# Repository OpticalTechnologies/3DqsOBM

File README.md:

This repository contains Matlab scripts for refractive index reconstruction, simulation of the DPLD, and KiCAD design
files for the detector read-out electronics used in the manuscript 
"Enabling 3D refractive index tomography in laser scanning microscopy with a simple tape-on detector".

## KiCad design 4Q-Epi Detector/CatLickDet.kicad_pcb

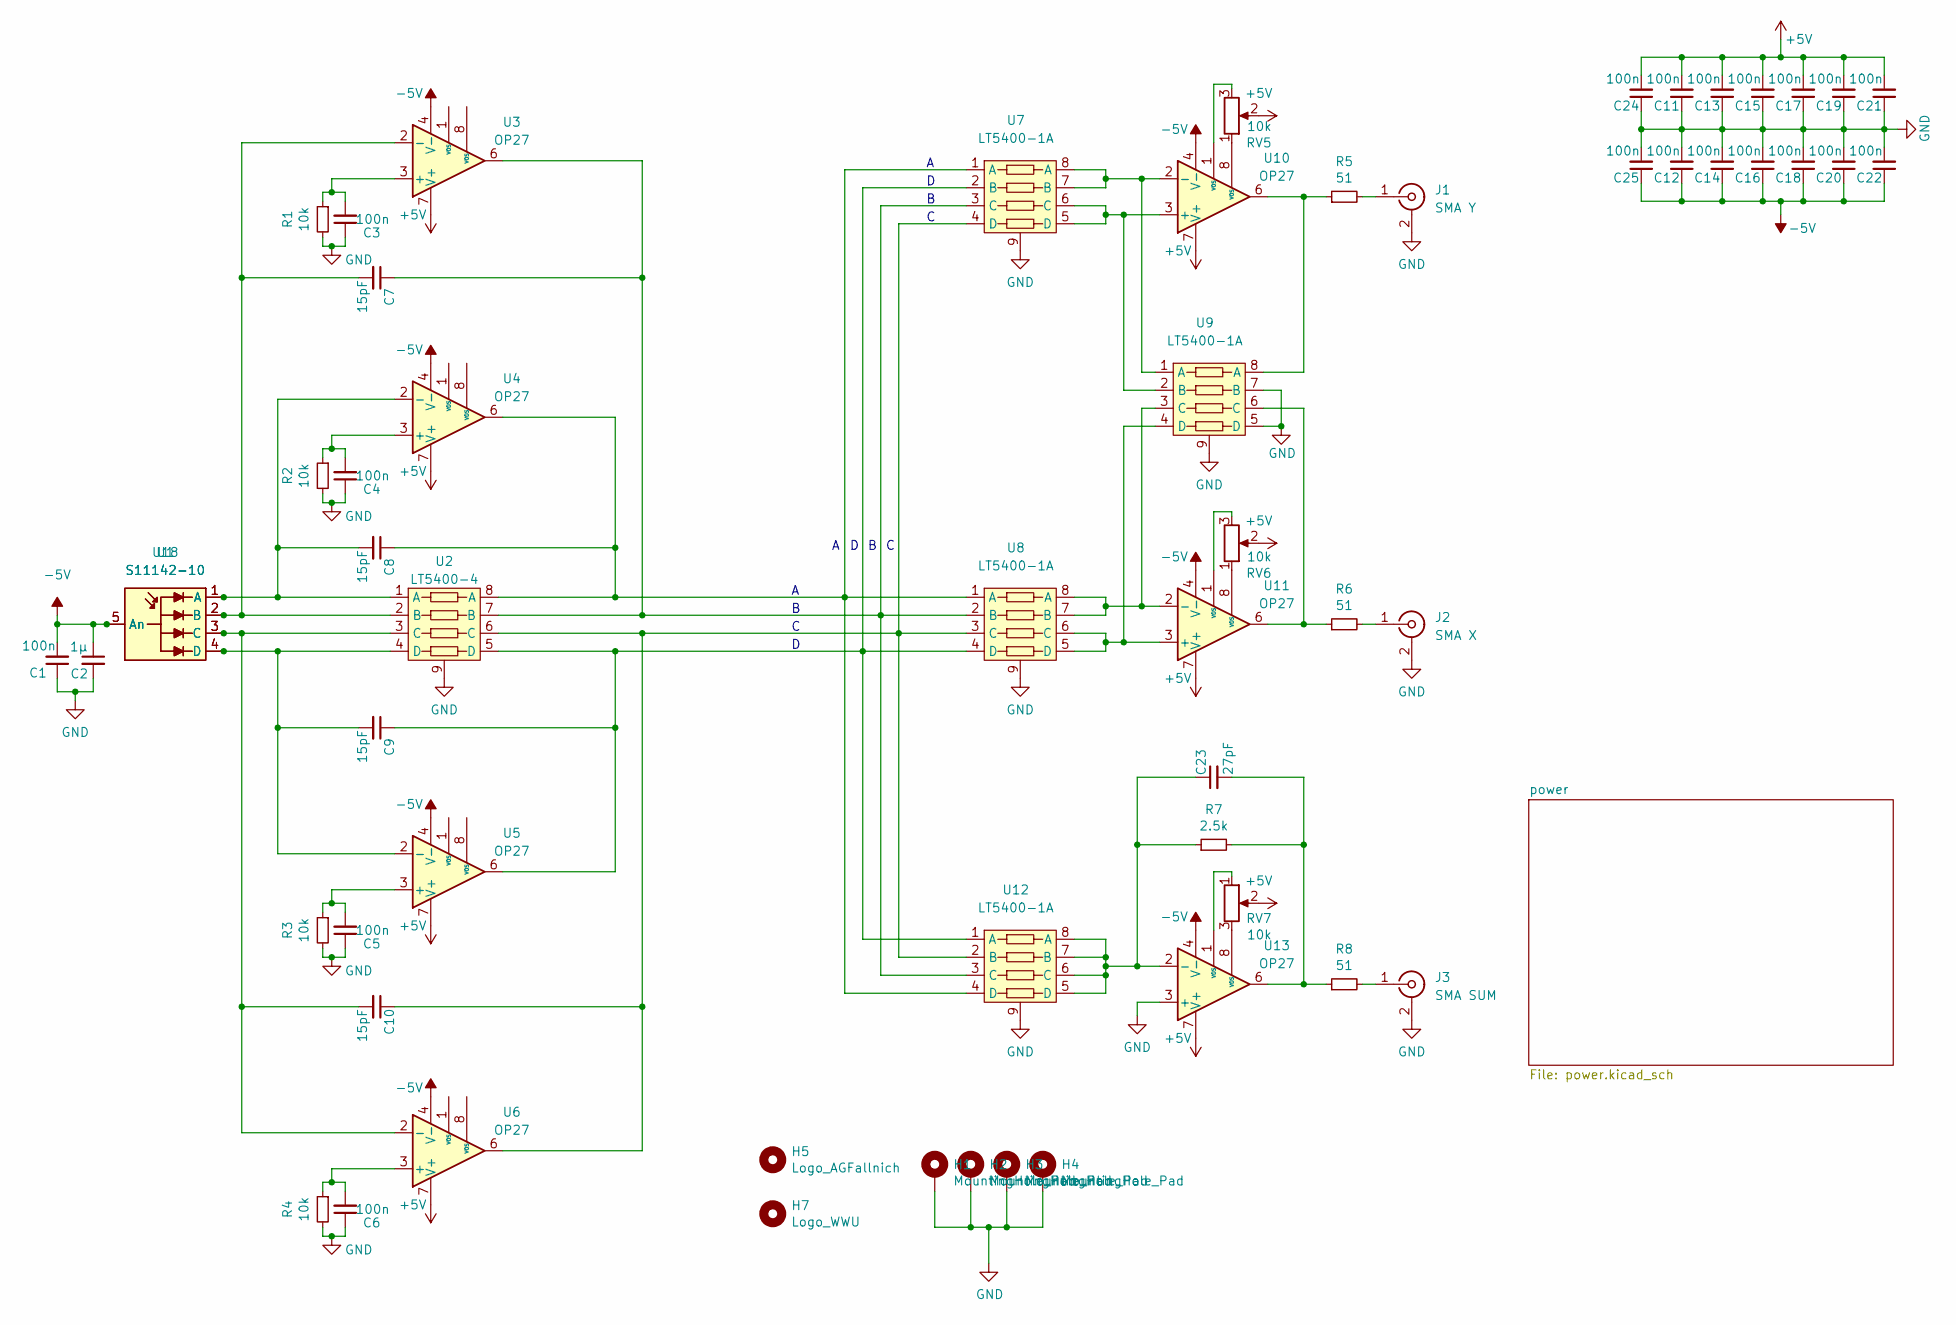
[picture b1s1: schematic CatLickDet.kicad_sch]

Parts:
C1, C3, C4, C5, C6, C11, C12, C13, C14, C15, C16, C17, C18, C19, C20, C21, C22, C24, C25: 100n; C_0402_1005Metric; LCSC C1525
C2: 1µ; C_0402_1005Metric; LCSC C52923
C7, C8, C9, C10: 15pF; C_0402_1005Metric; LCSC C1548
C23: 27pF; C_0402_1005Metric; LCSC C1557
H1, H2, H3, H4: MountingHole_Pad; MountingHole_3.2mm_M3_ISO7380_Pad
H5: Logo_AGFallnich; Logo_AGFallnich_text
H7: Logo_WWU
J1: SMA Y; SMA_Amphenol_132134-16_Vertical; Mouser 737-RF204AT0050G
J2: SMA X; SMA_Amphenol_132134-16_Vertical; Mouser 737-RF204AT0050G
J3: SMA SUM; SMA_Amphenol_132134-16_Vertical; Mouser 737-RF204AT0050G
R1, R2, R3, R4: 10k; R_0402_1005Metric; LCSC C190095
R5, R6, R8: 51; R_0402_1005Metric; LCSC C25125
R7: 2.5k; R_0603_1608Metric; LCSC C304065
RV5, RV6, RV7: 10k; Potentiometer_Bourns_3224W_Vertical; LCSC C81348
U1, U18: S11142-10
U2: LT5400-4; MSOP-8-1EP_3x3mm_P0.65mm_EP1.68x1.88mm; LCSC C1357905
U3, U4, U5, U6, U10, U11, U13: OP27; SOIC-8_3.9x4.9mm_P1.27mm; LCSC C581242
U7, U8, U9, U12: LT5400-1A; MSOP-8-1EP_3x3mm_P0.65mm_EP1.68x1.88mm; LCSC C1739156

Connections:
+5V: C11.2, C13.2, C15.2, C17.2, C19.2, C21.2, C24.2, RV5.2, RV6.2, RV7.2, U3.7 (V+), U4.7 (V+), U5.7 (V+), U6.7 (V+), U10.7 (V+), U11.7 (V+), U13.7 (V+); also elsewhere on the board
-5V: C1.2, C2.1, C12.1, C14.1, C16.1, C18.1, C20.1, C22.1, C25.1, U1.5 (An), U3.4 (V-), U4.4 (V-), U5.4 (V-), U6.4 (V-), U10.4 (V-), U11.4 (V-), U13.4 (V-), U18.5 (An); also elsewhere on the board
GND: C1.1, C2.2, C3.1, C4.1, C5.1, C6.1, C11.1, C12.2, C13.1, C14.2, C15.1, C16.2, C17.1, C18.2, C19.1, C20.2, C21.1, C22.2, C24.1, C25.2, H1.1, H2.1, H3.1, H4.1, J1.2 (Ext), J2.2 (Ext), J3.2 (Ext), R1.2, R2.2, R3.2, R4.2, U2.9, U7.9, U8.9, U9.5 (D), U9.7 (B), U9.9, U12.9, U13.3 (+); also elsewhere on the board
unnamed: C3.2, R1.1, U3.3 (+)
unnamed: C4.2, R2.1, U4.3 (+)
unnamed: C5.2, R3.1, U5.3 (+)
unnamed: C6.2, R4.1, U6.3 (+)
unnamed: C7.1, U2.7 (B), U3.6, U7.3 (C), U8.2 (B), U12.3 (C)
unnamed: C7.2, U1.2 (B), U2.2 (B), U3.2 (-), U18.2 (B)
unnamed: C8.1, U2.8 (A), U4.6, U7.1 (A), U8.1 (A), U12.4 (D)
unnamed: C8.2, U1.1 (A), U2.1 (A), U4.2 (-), U18.1 (A)
unnamed: C9.1, U2.5 (D), U5.6, U7.2 (B), U8.4 (D), U12.1 (A)
unnamed: C9.2, U1.4 (D), U2.4 (D), U5.2 (-), U18.4 (D)
unnamed: C10.1, U2.6 (C), U6.6, U7.4 (D), U8.3 (C), U12.2 (B)
unnamed: C10.2, U1.3 (C), U2.3 (C), U6.2 (-), U18.3 (C)
unnamed: C23.1, R7.1, U12.5 (D), U12.6 (C), U12.7 (B), U12.8 (A), U13.2 (-)
unnamed: C23.2, R7.2, R8.1, U13.6
unnamed: J1.1 (In), R5.2
unnamed: J2.1 (In), R6.2
unnamed: J3.1 (In), R8.2
unnamed: R5.1, U9.8 (A), U10.6
unnamed: R6.1, U9.6 (C), U11.6
unnamed: RV5.1, U10.8 (VOS)
unnamed: RV5.3, U10.1 (VOS)
unnamed: RV6.1, U11.8 (VOS)
unnamed: RV6.3, U11.1 (VOS)
unnamed: RV7.1, U13.1 (VOS)
unnamed: RV7.3, U13.8 (VOS)
unnamed: U7.7 (B), U7.8 (A), U9.1 (A), U10.2 (-)
unnamed: U7.5 (D), U7.6 (C), U9.2 (B), U10.3 (+)
unnamed: U8.7 (B), U8.8 (A), U9.3 (C), U11.2 (-)
unnamed: U8.5 (D), U8.6 (C), U9.4 (D), U11.3 (+)

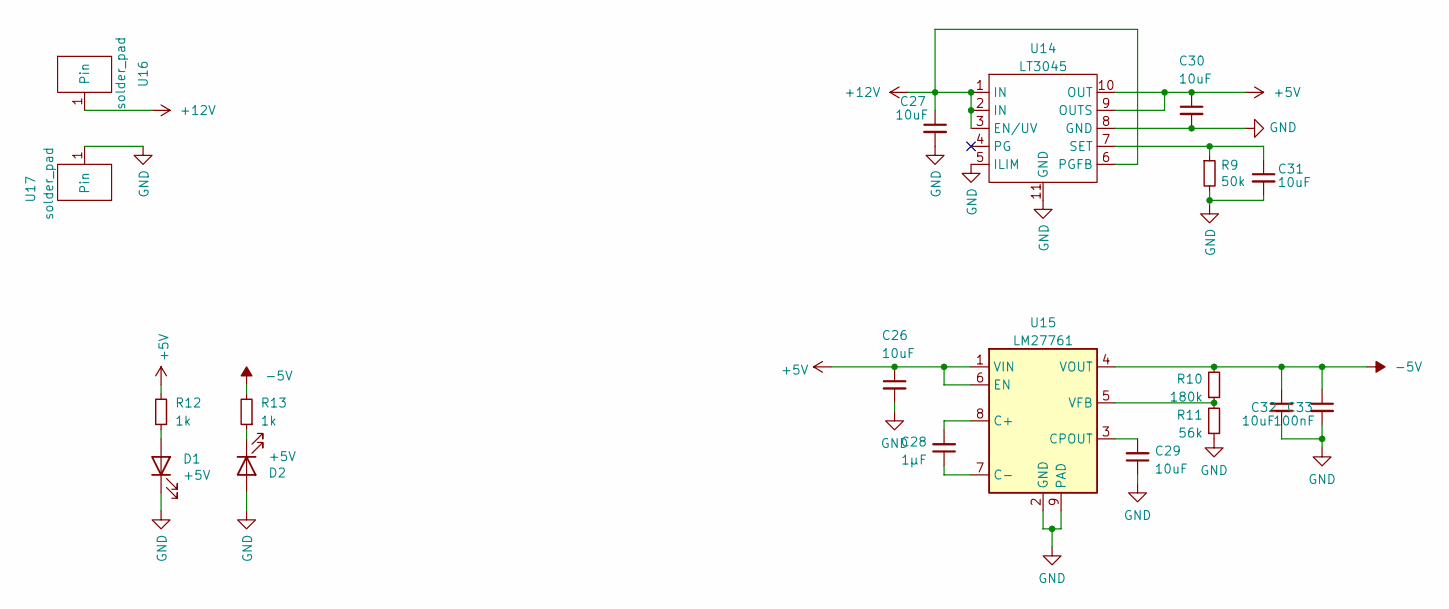
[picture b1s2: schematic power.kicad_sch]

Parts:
C26, C27, C30, C31, C32: 10uF; C_1206_3216Metric; LCSC C13585
C28: 1µF; C_0402_1005Metric; LCSC C52923
C29: 10uF; C_0402_1005Metric; LCSC C386033
C33: 100nF; C_0402_1005Metric; LCSC C307331
D1, D2: +5V; LED_0603_1608Metric; LCSC C2286
R9: 50k; R_0402_1005Metric; LCSC C25794
R10: 180k; R_0402_1005Metric; LCSC C138046
R11: 56k; R_0402_1005Metric; LCSC C25796
R12, R13: 1k; R_0402_1005Metric; LCSC C328418
U14: LT3045; DFN-10-1EP_3x3mm_P0.5mm_EP1.65x2.38mm; LCSC C666574
U15: LM27761; WSON-8-1EP_2x2mm_P0.5mm_EP0.9x1.6mm; LCSC C129351
U16, U17: solder_pad

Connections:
+5V: C26.1, C30.1, R12.2, U14.9 (OUTS), U14.10 (OUT), U15.1 (VIN), U15.6 (EN); also elsewhere on the board
+12V: C27.1, U14.1 (IN), U14.2 (IN), U14.3 (EN/UV), U14.6 (PGFB), U16.1
-5V: C32.1, C33.1, R10.2, R13.2, U15.4 (VOUT); also elsewhere on the board
GND: C26.2, C27.2, C29.1, C30.2, C31.2, C32.2, C33.2, D1.1 (K), D2.2 (A), R9.2, R11.1, U14.5 (ILIM), U14.8 (GND), U14.11 (GND), U15.2 (GND), U15.9 (PAD), U17.1; also elsewhere on the board
unnamed: C28.1, U15.7 (C-)
unnamed: C28.2, U15.8 (C+)
unnamed: C29.2, U15.3 (CPOUT)
unnamed: C31.1, R9.1, U14.7 (SET)
unnamed: D1.2 (A), R12.1
unnamed: D2.1 (K), R13.1
unnamed: R10.1, R11.2, U15.5 (VFB)

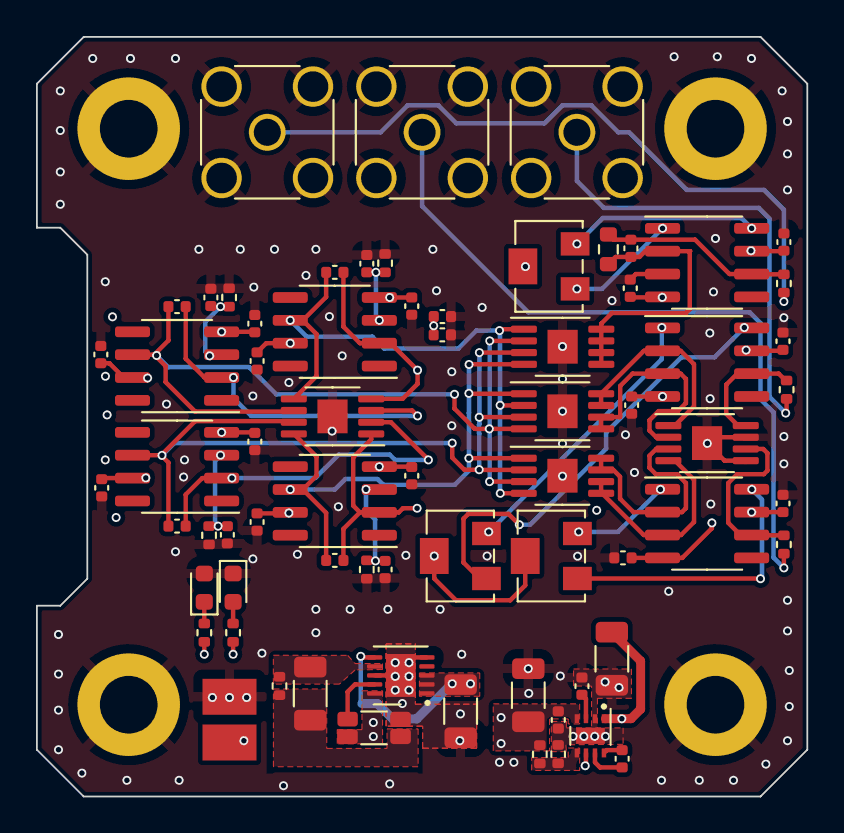
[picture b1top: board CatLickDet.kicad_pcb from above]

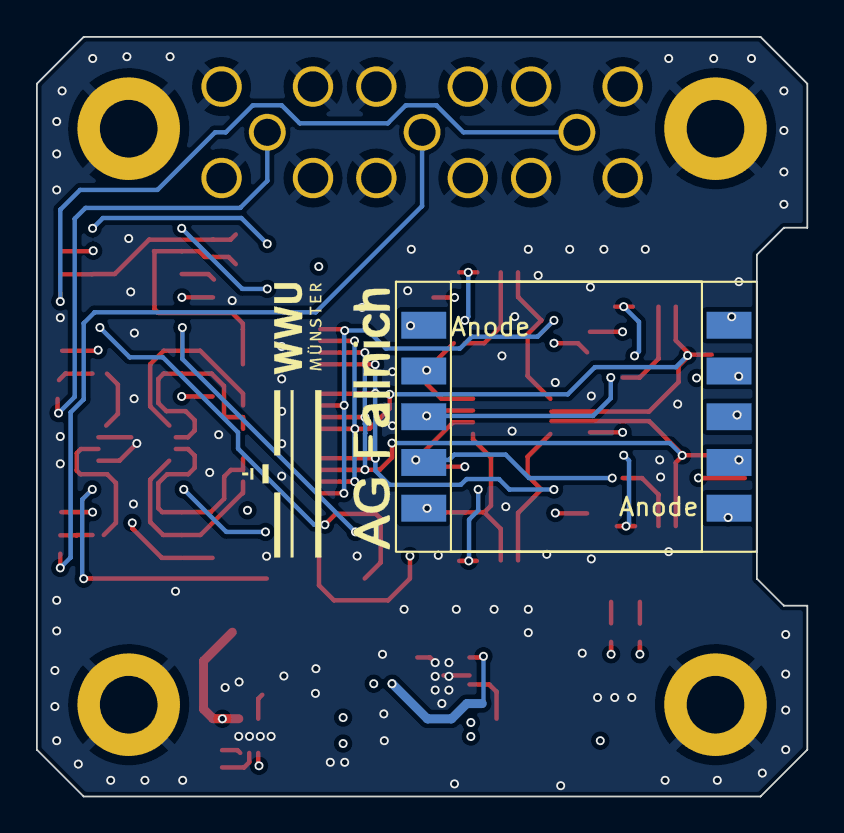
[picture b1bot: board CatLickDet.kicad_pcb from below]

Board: 4 copper layers, 42.8 x 42.2 mm, 78 parts (4 on the bottom side), 40 nets.

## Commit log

2026-05-20 Create LICENSE
